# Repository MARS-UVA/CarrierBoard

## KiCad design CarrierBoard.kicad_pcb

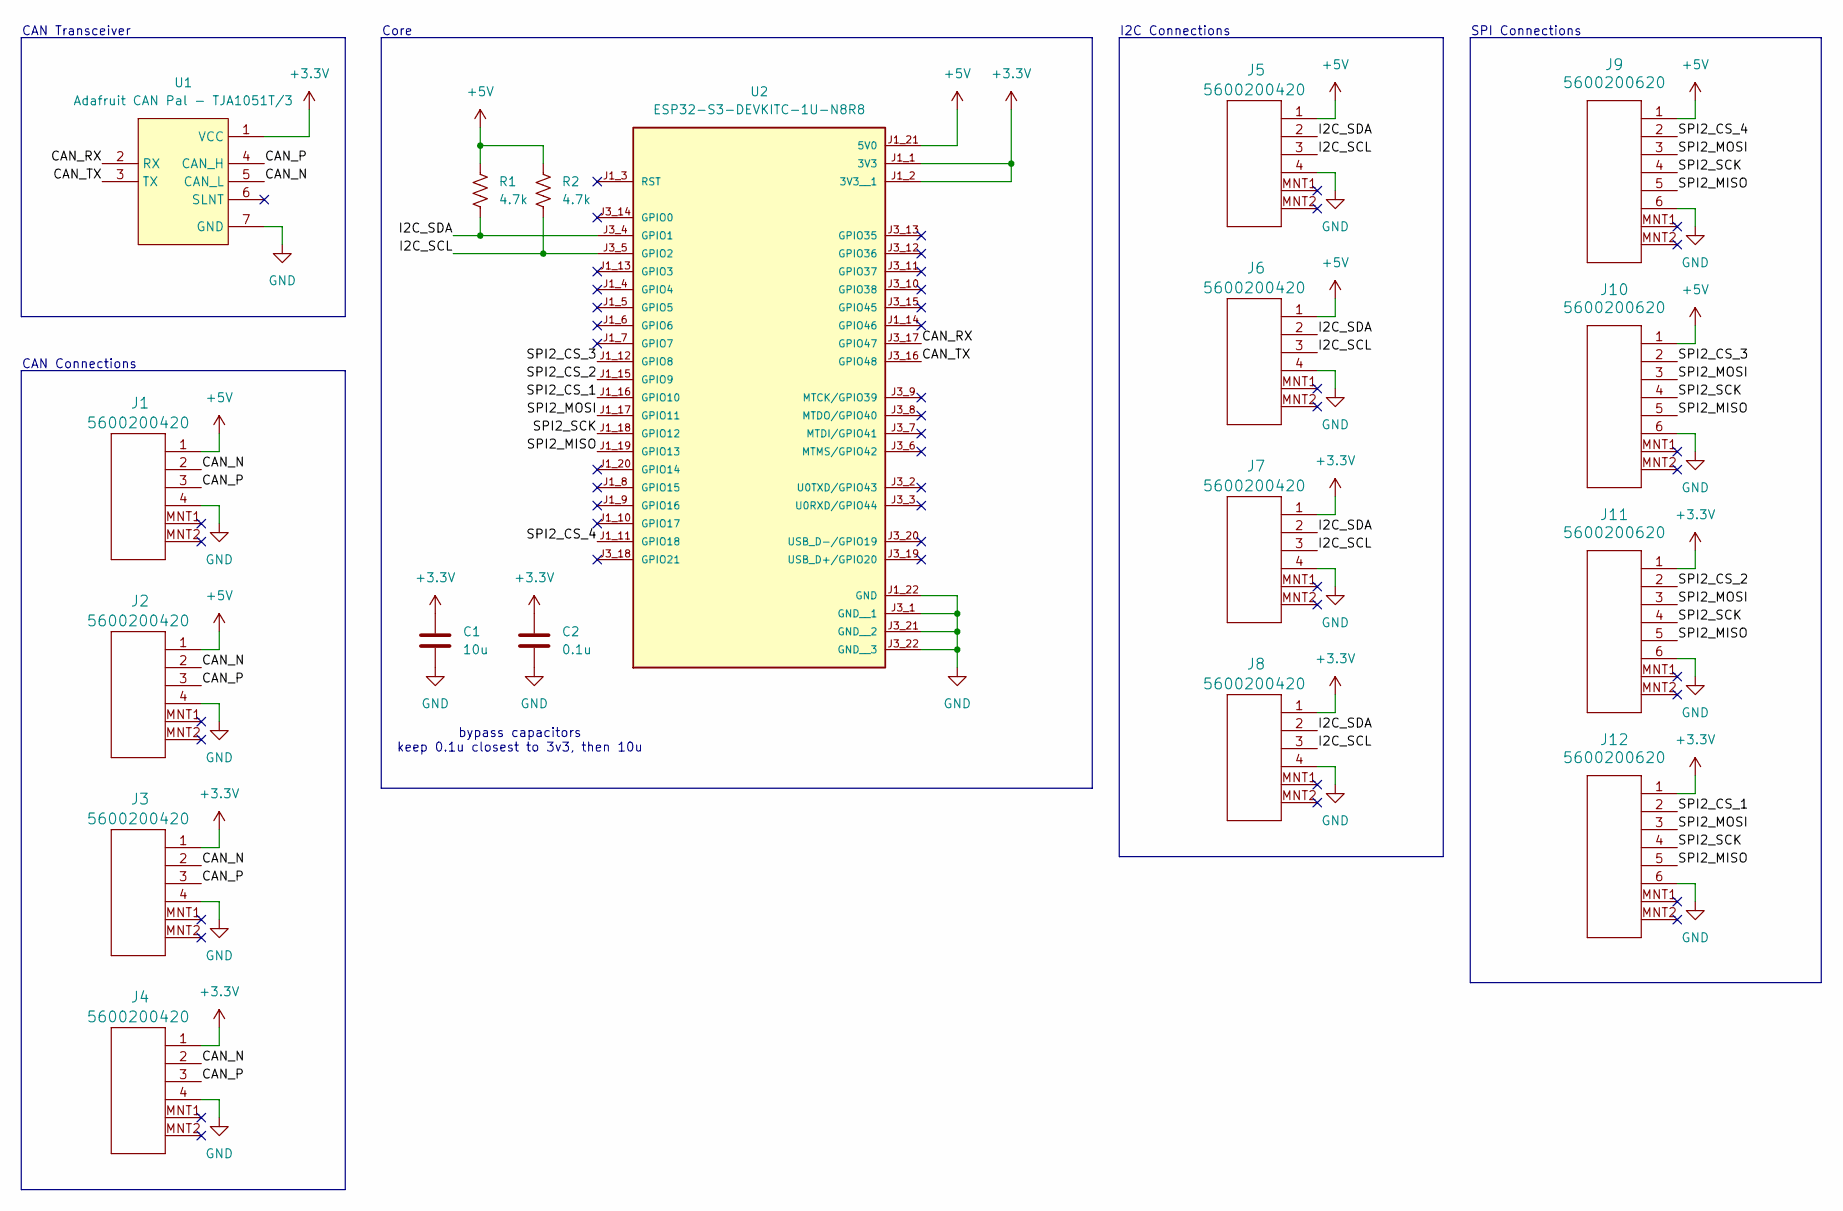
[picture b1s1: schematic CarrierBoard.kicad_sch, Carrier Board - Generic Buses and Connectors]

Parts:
C1: 10u; C_0603_1608Metric; Part Number LMK107BBJ106MALT
C2: 0.1u; C_0603_1608Metric; Part Number LMK107BBJ106MALT
J1, J2, J3, J4, J5, J6, J7, J8: 5600200420; CONN_SD-560020-001_04_MOL
J9, J10, J11, J12: 5600200620; CONN_SD-560020-001_06_MOL
R1, R2: 4.7k; R_0603_1608Metric; Part Number RC0603FR-073K3L
U1: Adafruit CAN Pal - TJA1051T/3; Adafruit CAN Pal - TJA1051T_3
U2: ESP32-S3-DEVKITC-1U-N8R8; PARTREV 1.1

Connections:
+3.3V: C1.1, C2.1, J3.1, J4.1, J7.1, J8.1, J11.1, J12.1, U1.1 (VCC), U2.J1_1 (3V3), U2.J1_2 (3V3__1)
+5V: J1.1, J2.1, J5.1, J6.1, J9.1, J10.1, R1.1, R2.1, U2.J1_21 (5V0)
/CAN_N: J1.2, J2.2, J3.2, J4.2, U1.5 (CAN_L)
/CAN_P: J1.3, J2.3, J3.3, J4.3, U1.4 (CAN_H)
/CAN_RX: U1.2 (RX), U2.J3_17 (GPIO47)
/CAN_TX: U1.3 (TX), U2.J3_16 (GPIO48)
/I2C_SCL: J5.3, J6.3, J7.3, J8.3, R2.2, U2.J3_5 (GPIO2)
/I2C_SDA: J5.2, J6.2, J7.2, J8.2, R1.2, U2.J3_4 (GPIO1)
/SPI2_CS_1: J12.2, U2.J1_16 (GPIO10)
/SPI2_CS_2: J11.2, U2.J1_15 (GPIO9)
/SPI2_CS_3: J10.2, U2.J1_12 (GPIO8)
/SPI2_CS_4: J9.2, U2.J1_11 (GPIO18)
/SPI2_MISO: J9.5, J10.5, J11.5, J12.5, U2.J1_19 (GPIO13)
/SPI2_MOSI: J9.3, J10.3, J11.3, J12.3, U2.J1_17 (GPIO11)
/SPI2_SCK: J9.4, J10.4, J11.4, J12.4, U2.J1_18 (GPIO12)
GND: C1.2, C2.2, J1.4, J2.4, J3.4, J4.4, J5.4, J6.4, J7.4, J8.4, J9.6, J10.6, J11.6, J12.6, U1.7 (GND), U2.J1_22 (GND), U2.J3_1 (GND__1), U2.J3_21 (GND__2), U2.J3_22 (GND__3)

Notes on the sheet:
CAN Transceiver
Core
CAN Connections
I2C Connections
bypass capacitors keep 0.1u closest to 3v3, then 10u
SPI Connections

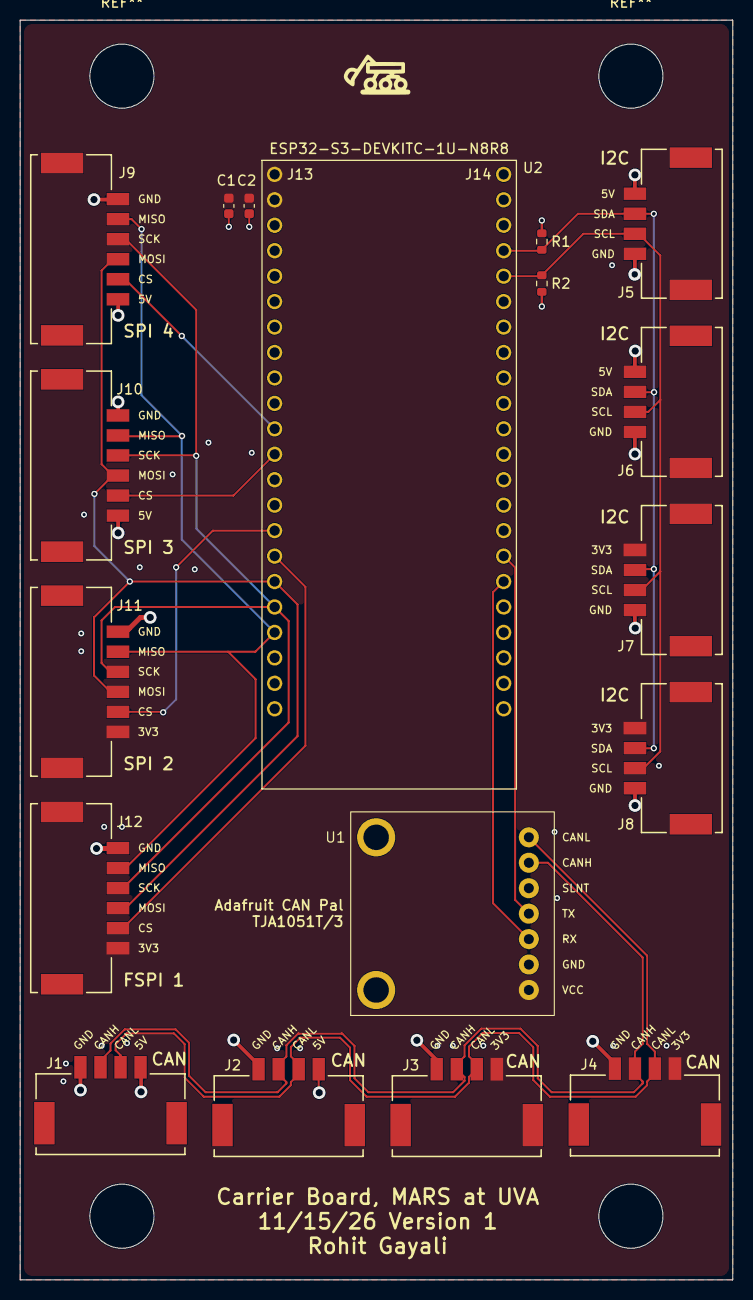
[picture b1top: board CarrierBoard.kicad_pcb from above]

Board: 4 copper layers, 71.1 x 125.7 mm, 18 parts (0 on the bottom side), 16 nets.
